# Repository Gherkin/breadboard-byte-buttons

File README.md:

# breadboard-byte-buttons
A small board for mounting in a breadboard with 2 8-bit DIP switches 
ibom: https://gherkin.github.io/breadboard-byte-buttons/

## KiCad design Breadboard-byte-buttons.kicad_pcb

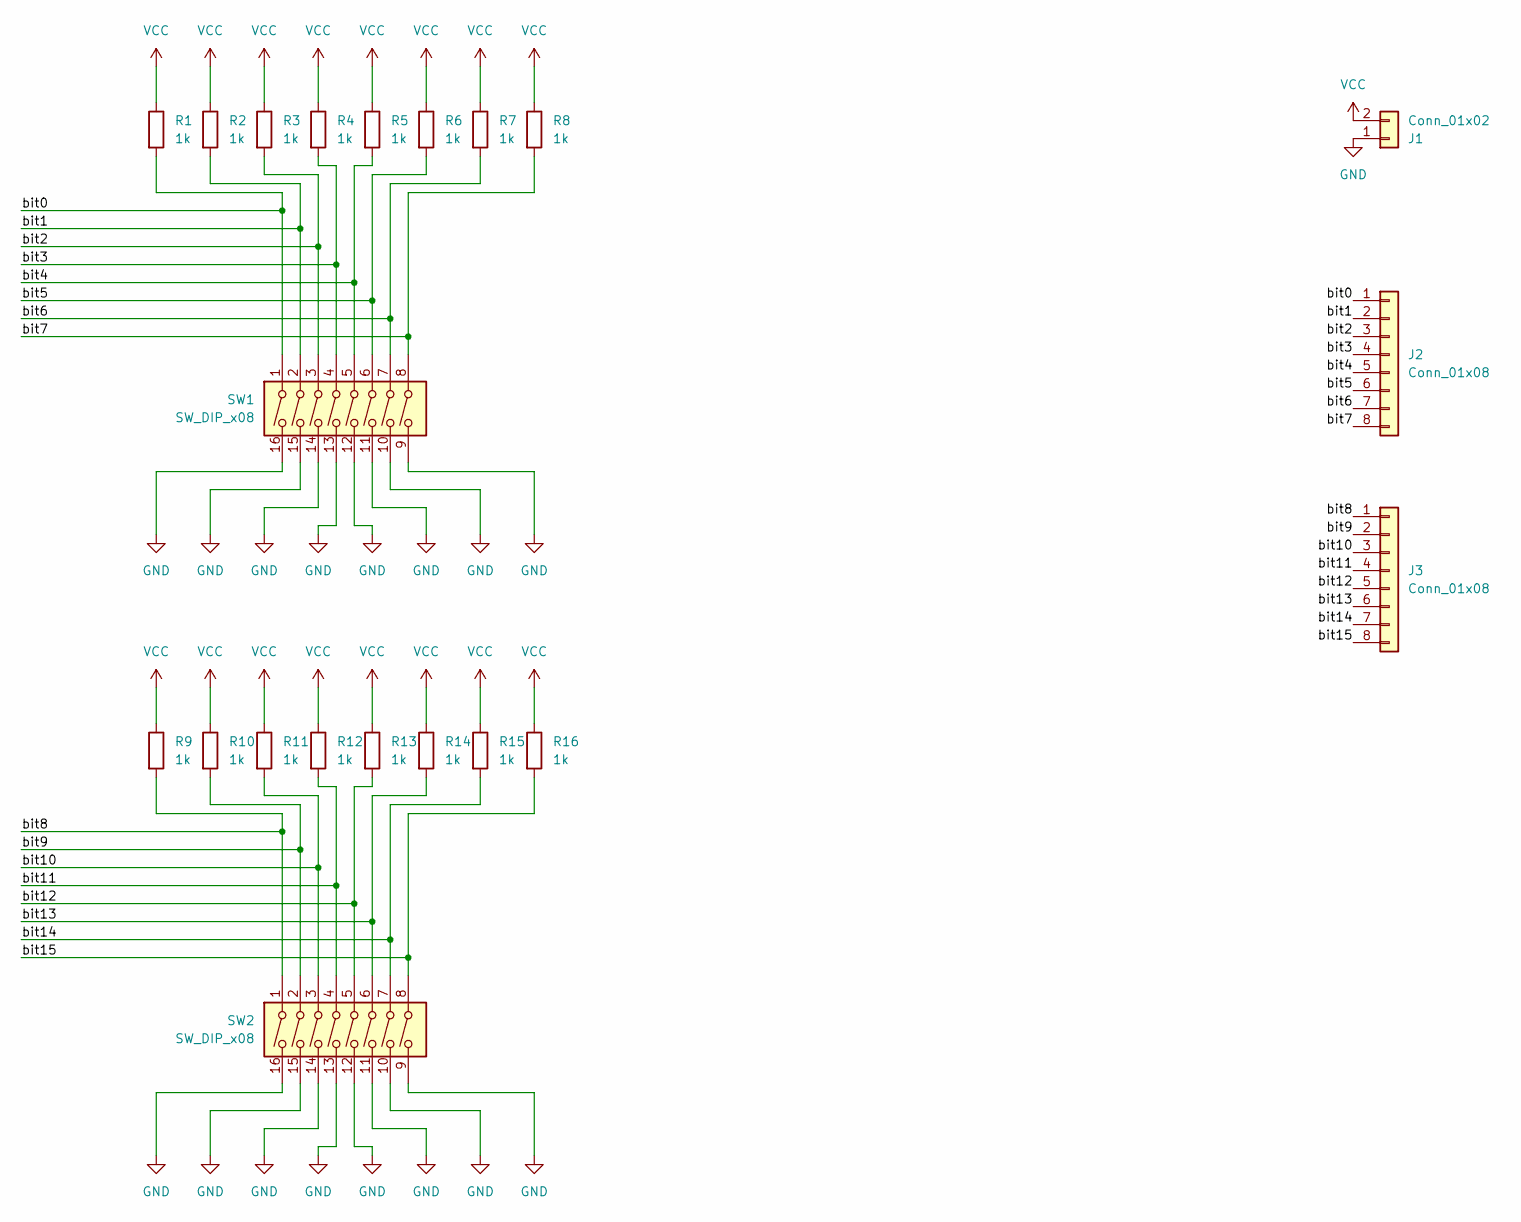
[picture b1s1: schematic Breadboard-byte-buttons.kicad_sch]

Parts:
J1: Conn_01x02; PinHeader_1x02_P2.54mm_Vertical
J2, J3: Conn_01x08; PinHeader_1x08_P2.54mm_Vertical
R1, R2, R3, R4, R5, R6, R7, R8, R9, R10, R11, R12, R13, R14, R15, R16: 1k; R_0402_1005Metric
SW1, SW2: SW_DIP_x08; SW_DIP_SPSTx08_Slide_6.7x21.88mm_W7.62mm_P2.54mm_LowProfile; LCSC C99413

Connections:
/bit0: J2.1, R1.2, SW1.1
/bit1: J2.2, R2.2, SW1.2
/bit2: J2.3, R3.2, SW1.3
/bit3: J2.4, R4.2, SW1.4
/bit4: J2.5, R5.2, SW1.5
/bit5: J2.6, R6.2, SW1.6
/bit6: J2.7, R7.2, SW1.7
/bit7: J2.8, R8.2, SW1.8
/bit8: J3.1, R9.2, SW2.1
/bit9: J3.2, R10.2, SW2.2
/bit10: J3.3, R11.2, SW2.3
/bit11: J3.4, R12.2, SW2.4
/bit12: J3.5, R13.2, SW2.5
/bit13: J3.6, R14.2, SW2.6
/bit14: J3.7, R15.2, SW2.7
/bit15: J3.8, R16.2, SW2.8
GND: J1.1, SW1.9, SW1.10, SW1.11, SW1.12, SW1.13, SW1.14, SW1.15, SW1.16, SW2.9, SW2.10, SW2.11, SW2.12, SW2.13, SW2.14, SW2.15, SW2.16
VCC: J1.2, R1.1, R2.1, R3.1, R4.1, R5.1, R6.1, R7.1, R8.1, R9.1, R10.1, R11.1, R12.1, R13.1, R14.1, R15.1, R16.1

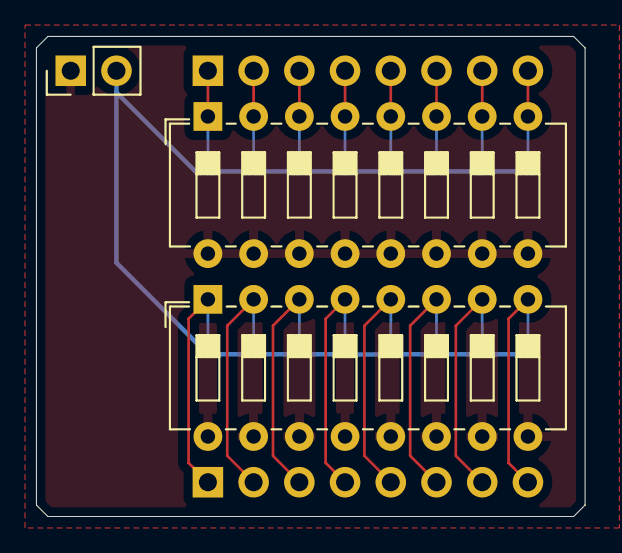
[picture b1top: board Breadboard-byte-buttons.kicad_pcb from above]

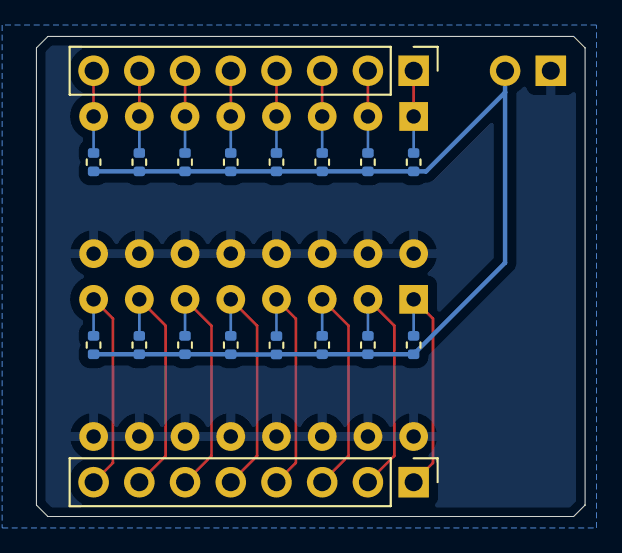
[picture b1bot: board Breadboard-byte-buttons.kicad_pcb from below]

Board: 2 copper layers, 30.5 x 26.7 mm, 21 parts (18 on the bottom side), 18 nets.

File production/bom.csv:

Designator,Footprint,Quantity,Value,LCSC Part #
J1,PinHeader_1x02_P2.54mm_Vertical,1,Conn_01x02,
"J2, J3",PinHeader_1x08_P2.54mm_Vertical,2,Conn_01x08,
"R1, R10, R11, R12, R13, R14, R15, R16, R2, R3, R4, R5, R6, R7, R8, R9",0402,16,1k,
"SW1, SW2",SW_DIP_SPSTx08_Slide_6.7x21.88mm_W7.62mm_P2.54mm_LowProfile,2,SW_DIP_x08,

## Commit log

2024-05-22 init
2024-05-22 more trailing spaces
2024-05-22 added ibom
2024-05-22 trailing spaces bc markdown
